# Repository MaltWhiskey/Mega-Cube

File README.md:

# Mega-Cube
16x16x16 PL9823 Cube with Teensy 4.0 and FlexIO driver
https://youtu.be/ciaFar8nfHc

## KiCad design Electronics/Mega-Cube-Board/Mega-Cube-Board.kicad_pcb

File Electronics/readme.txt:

Disclamer:
    These are my own electronic designs. You can use them however you like, but i take no
    responsibilty for them. It's up to you to use them well. 

Versions:
    32Bit shift register - This is my first iterration, i had some problems with them due to
    high frequency signals and using wires instead of pcb traces resulting in reflections.
    I have changed the software/hardware interface, so these may work, but i haven't tested this.

    32Bit shift register - This is the 2nd iterration. Fixed the reflexions and works flaweless
    for me. I recommond using JXT XH connectors and not dupont, since the touch screen can't handle
    iffy wiring. Just put a big cap i use 470uF near the power input. Other components are smd and
    you can have them assembled.
    Upload the Gerbers "32bit sr v2.0.zip" from the "32Bit SR Gerbers" folder to jlcpcb.com
    Turn on pcb assembly
    Upload the BOM-file "32Bit shift register.xlsx" from the "32Bit SR Assembly" folder
    Upload the CPL-file "32Bit shift register-all-pos.xlsx" from the "32Bit SR Assembly" folder
    Verify the components are in stock and place correctly.
    Order pcb

    Mega-Cube-Board - I wanted more functionality so i developed this board. The LCD can be soldered
    directly on this board without wires, so has more stability. It also has a buck converter and
    esp32's on it for gaming. A microphone and can drive speakers. The price to order this board
    was over $100 so i stopped working on it.

WARNING:
    The teensy 4.0 has no protection on the USB power. So powering through USB and a power supply
    may blow things up (I don't know because i'm carefull). You can use a usb cable and cut the 5V
    line. Or solder in a diode somewhere (look on pjrc site how to do that). Also never connect the
    5V power from the supplies together (I don't know what will happen, but probably real fireworks)
    All grounds from all power supplies must be tied together (NOT to the earth protective ground)
    If things are flickering you most likely have a disconnected wire or a grounding issue somewhere.

    Hope this clears thing up. Happy soldering.
    Malt Whiskey

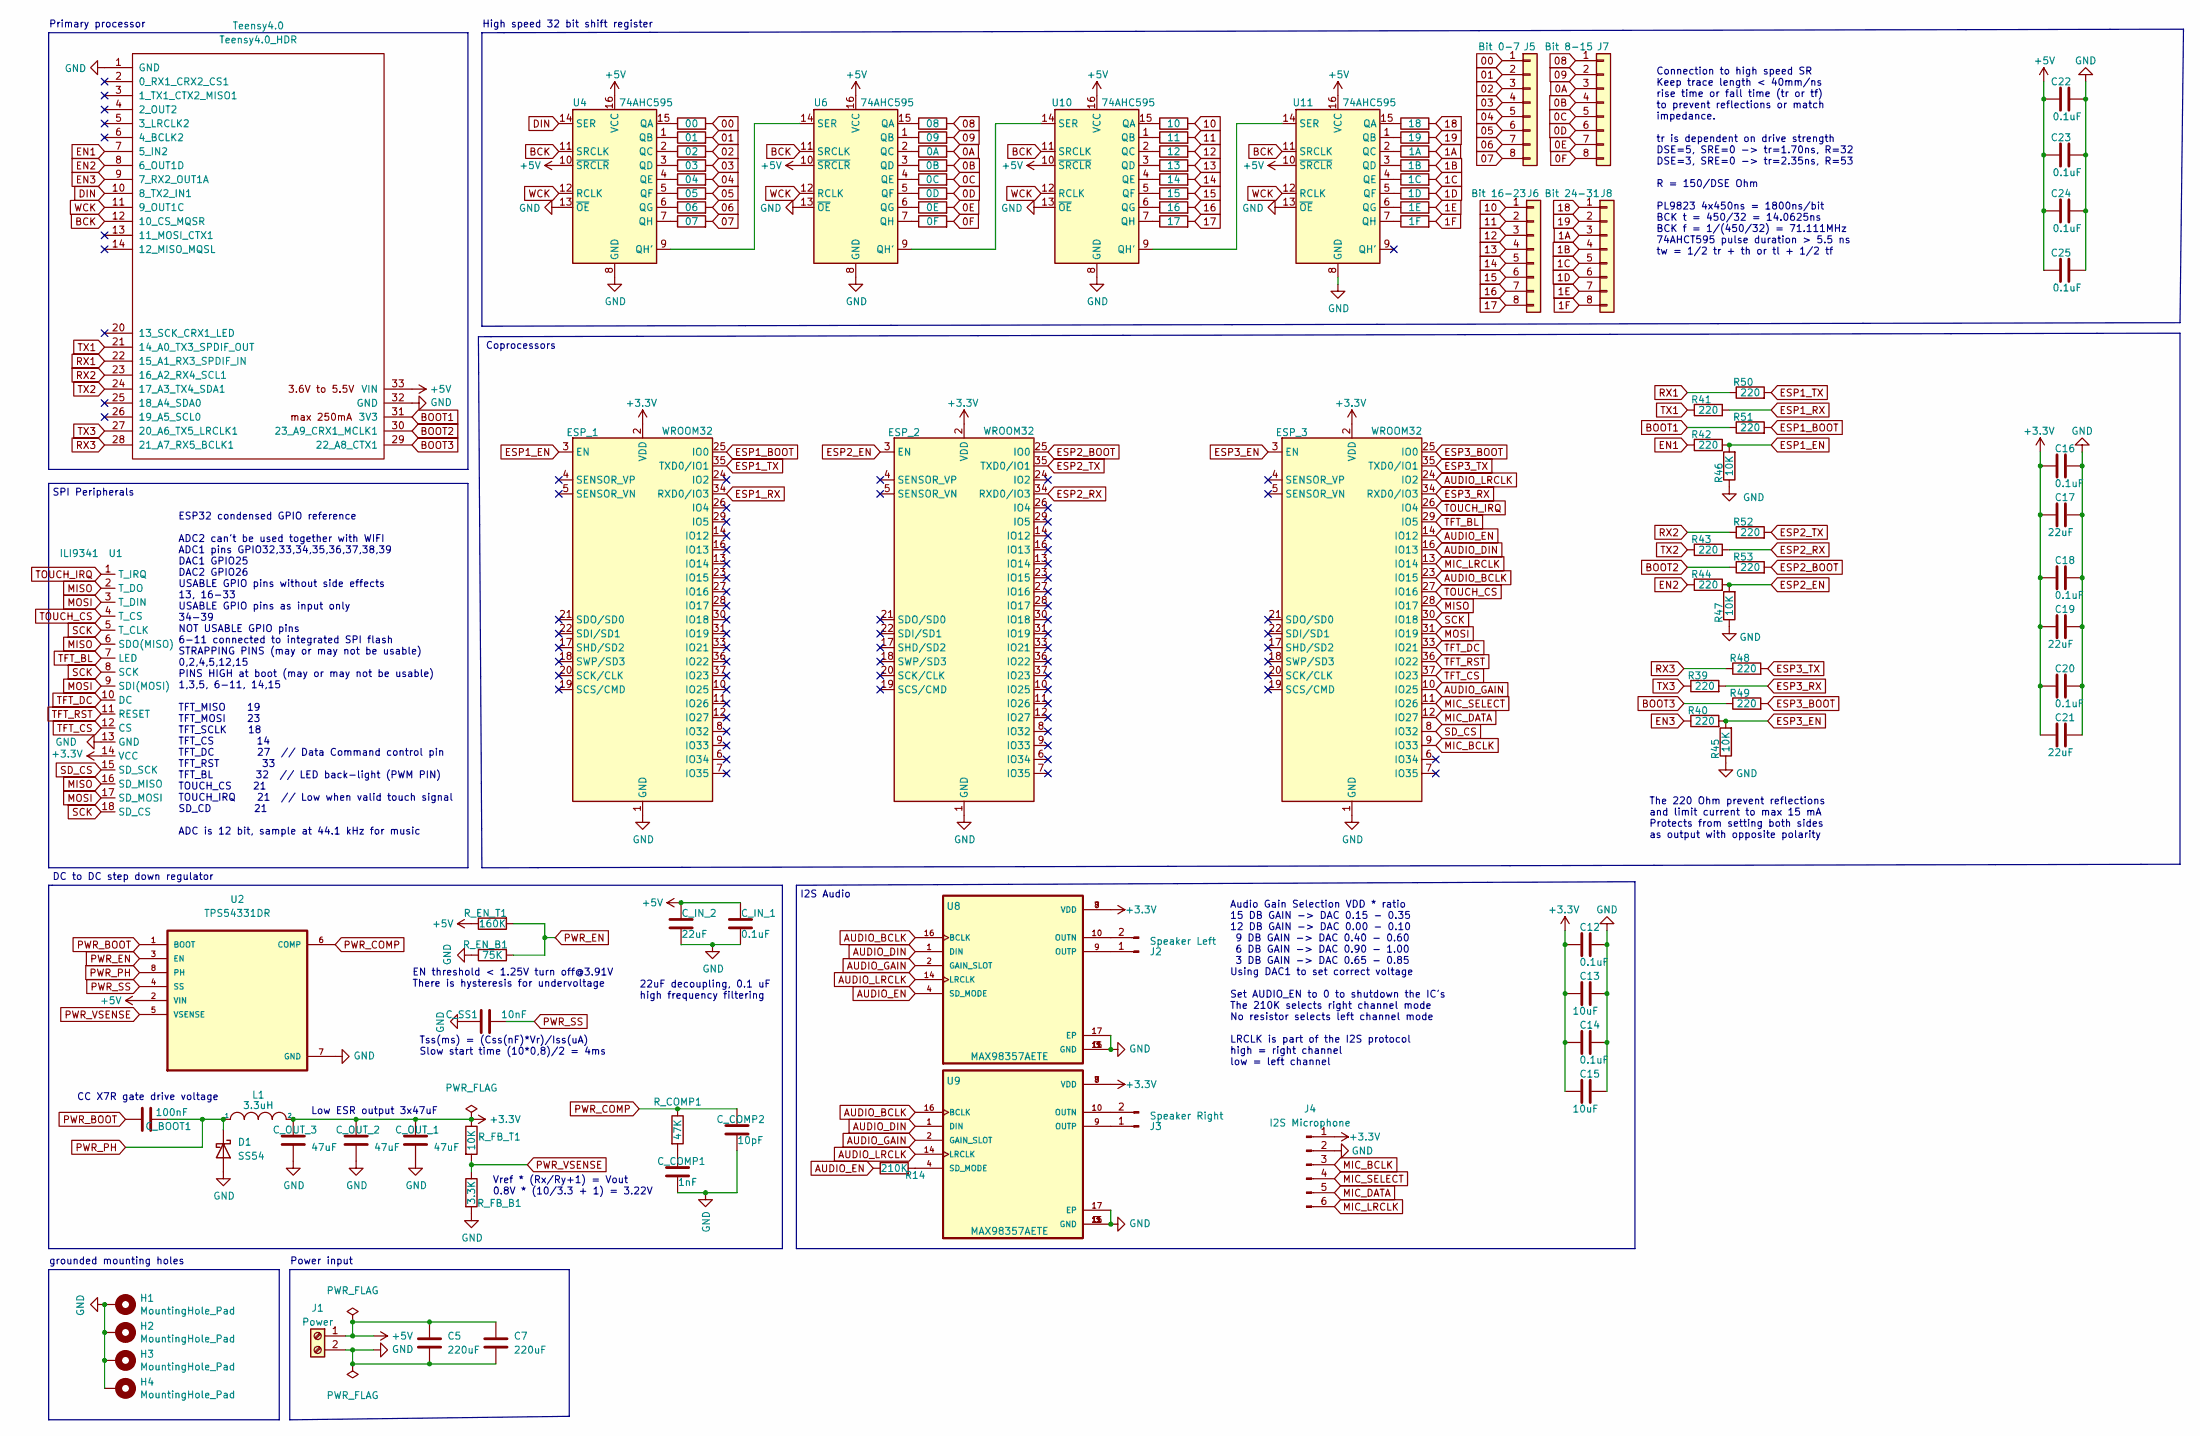
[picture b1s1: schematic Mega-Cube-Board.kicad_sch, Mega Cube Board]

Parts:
C5, C7: 220uF; CP_Radial_D8.0mm_P2.50mm
C12, C14: 0.1uF; C_0402_1005Metric; LCSC Part C307331
C13, C15: 10uF; C_0402_1005Metric; LCSC Part C15525
C16, C18, C20, C22, C23, C24, C25: 0.1uF; C_0603_1608Metric; LCSC Part C14663
C17, C19, C21: 22uF; C_0603_1608Metric; LCSC Part C59461
C_BOOT1: 100nF; C_0603_1608Metric; LCSC Part C14663
C_COMP1: 1nF; C_0603_1608Metric; LCSC Part C1588
C_COMP2: 10pF; C_0603_1608Metric; LCSC Part C1634
C_IN_1: 0.1uF; C_1206_3216Metric; LCSC Part C24497
C_IN_2: 22uF; C_1206_3216Metric; LCSC Part C12891
C_OUT_1, C_OUT_2, C_OUT_3: 47uF; C_1206_3216Metric; LCSC Part C96123
C_SS1: 10nF; C_0603_1608Metric; LCSC Part C57112
D1: SS54; D_SMA; LCSC Part C22452
ESP_1, ESP_2, ESP_3: WROOM32; ESP32-WROOM-32; LCSC Part C82899
H1, H2, H3, H4: MountingHole_Pad; MountingHole_3.2mm_M3_Pad_Via
J1: Power; TerminalBlock_bornier-2_P5.08mm
J2: Speaker Left; JST_XH_B2B-XH-A_1x02_P2.50mm_Vertical
J3: Speaker Right; JST_XH_B2B-XH-A_1x02_P2.50mm_Vertical
J4: I2S Microphone; JST_XH_B6B-XH-A_1x06_P2.50mm_Vertical
J5: Bit 0-7; JST_XH_B8B-XH-A_1x08_P2.50mm_Vertical
J6: Bit 16-23; JST_XH_B8B-XH-A_1x08_P2.50mm_Vertical
J7: Bit 8-15; JST_XH_B8B-XH-A_1x08_P2.50mm_Vertical
J8: Bit 24-31; JST_XH_B8B-XH-A_1x08_P2.50mm_Vertical
L1: 3.3uH; L_Sunltech_SLO0630H_7.1x6.6mm; LCSC Part C207839
R6, R7, R8, R9, R10, R11, R12, R13, R15, R16, R17, R18, R19, R20, R21, R22, R23, R24, R25, R26, R27, R28, R29, R30, R31, R32, R33, R34, R35, R36, R37, R38, R39, R40, R41, R42, R43, R44, R48, R49, R50, R51, R52, R53: 220; R_0402_1005Metric; LCSC Part C25091
R14: 210K; R_0402_1005Metric; LCSC Part C25767
R45, R46, R47: 10K; R_0402_1005Metric; LCSC Part C25744
R_COMP1: 47K; R_0603_1608Metric; LCSC Part C25819
R_EN_B1: 75K; R_0603_1608Metric; LCSC Part C23242
R_EN_T1: 160K; R_0603_1608Metric; LCSC Part C22813
R_FB_B1: 3.3K; R_0603_1608Metric; LCSC Part C22978
R_FB_T1: 10K; R_0603_1608Metric; LCSC Part C25804
Teensy4.0: Teensy4.0_HDR; Teensy40hdr
U1: ILI9341; ILI9341 2.4 TFT
U2: TPS54331DR; SOIC127P599X175-8N; LCSC Part C9865
U4, U6, U10, U11: 74AHC595; SOIC-16_3.9x9.9mm_P1.27mm; LCSC Part C133793
U8, U9: MAX98357AETE; QFN50P300X300X80-17N; LCSC Part C910544

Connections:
00: J5.1, R6.2
0A: J7.3, R17.2
0B: J7.4, R18.2
0C: J7.5, R19.2
0D: J7.6, R20.2
0E: J7.7, R21.2
0F: J7.8, R22.2
01: J5.2, R7.2
1A: J8.3, R33.2
1B: J8.4, R34.2
1C: J8.5, R35.2
1D: J8.6, R36.2
1E: J8.7, R37.2
1F: J8.8, R38.2
02: J5.3, R8.2
03: J5.4, R9.2
04: J5.5, R10.2
05: J5.6, R11.2
06: J5.7, R12.2
07: J5.8, R13.2
08: J7.1, R15.2
09: J7.2, R16.2
10: J6.1, R23.2
11: J6.2, R24.2
12: J6.3, R25.2
13: J6.4, R26.2
14: J6.5, R27.2
15: J6.6, R28.2
16: J6.7, R29.2
17: J6.8, R30.2
18: J8.1, R31.2
19: J8.2, R32.2
+3V3: C12.2, C13.2, C14.2, C15.2, C16.2, C17.2, C18.2, C19.2, C20.2, C21.2, C_OUT_1.1, C_OUT_2.1, C_OUT_3.1, ESP_1.2 (VDD), ESP_2.2 (VDD), ESP_3.2 (VDD), J4.1, L1.2, R_FB_T1.1, U1.14 (VCC), U8.7 (VDD), U8.8 (VDD), U9.7 (VDD), U9.8 (VDD)
+5V: C5.1, C7.1, C22.1, C23.1, C24.1, C25.1, C_IN_1.1, C_IN_2.1, J1.1, R_EN_T1.1, Teensy4.0.33 (VIN), U2.2 (VIN), U4.10 (~SRCLR), U4.16 (VCC), U6.10 (~SRCLR), U6.16 (VCC), U10.10 (~SRCLR), U10.16 (VCC), U11.10 (~SRCLR), U11.16 (VCC)
AUDIO_BCLK: ESP_3.23 (IO15), U8.16 (BCLK), U9.16 (BCLK)
AUDIO_DIN: ESP_3.16 (IO13), U8.1 (DIN), U9.1 (DIN)
AUDIO_EN: ESP_3.14 (IO12), R14.1, U8.4 (SD_MODE)
AUDIO_GAIN: ESP_3.10 (IO25), U8.2 (GAIN_SLOT), U9.2 (GAIN_SLOT)
AUDIO_LRCLK: ESP_3.24 (IO2), U8.14 (LRCLK), U9.14 (LRCLK)
BCK: Teensy4.0.12 (10_CS_MQSR), U4.11 (SRCLK), U6.11 (SRCLK), U10.11 (SRCLK), U11.11 (SRCLK)
BOOT1: R51.1, Teensy4.0.31 (3V3)
BOOT2: R53.1, Teensy4.0.30 (23_A9_CRX1_MCLK1)
BOOT3: R49.1, Teensy4.0.29 (22_A8_CTX1)
DIN: Teensy4.0.10 (8_TX2_IN1), U4.14 (SER)
EN1: R42.1, Teensy4.0.7 (5_IN2)
EN2: R44.1, Teensy4.0.8 (6_OUT1D)
EN3: R40.1, Teensy4.0.9 (7_RX2_OUT1A)
ESP1_BOOT: ESP_1.25 (IO0), R51.2
ESP1_EN: ESP_1.3 (EN), R42.2, R46.2
ESP1_RX: ESP_1.34 (RXD0/IO3), R41.2
ESP1_TX: ESP_1.35 (TXD0/IO1), R50.2
ESP2_BOOT: ESP_2.25 (IO0), R53.2
ESP2_EN: ESP_2.3 (EN), R44.2, R47.2
ESP2_RX: ESP_2.34 (RXD0/IO3), R43.2
ESP2_TX: ESP_2.35 (TXD0/IO1), R52.2
ESP3_BOOT: ESP_3.25 (IO0), R49.2
ESP3_EN: ESP_3.3 (EN), R40.2, R45.2
ESP3_RX: ESP_3.34 (RXD0/IO3), R39.2
ESP3_TX: ESP_3.35 (TXD0/IO1), R48.2
GND: C5.2, C7.2, C12.1, C13.1, C14.1, C15.1, C16.1, C17.1, C18.1, C19.1, C20.1, C21.1, C22.2, C23.2, C24.2, C25.2, C_COMP1.2, C_COMP2.2, C_IN_1.2, C_IN_2.2, C_OUT_1.2, C_OUT_2.2, C_OUT_3.2, C_SS1.1, D1.2 (A), ESP_1.1 (GND), ESP_1.15 (GND), ESP_1.38 (GND), ESP_1.39 (GND), ESP_2.1 (GND), ESP_2.15 (GND), ESP_2.38 (GND), ESP_2.39 (GND), ESP_3.1 (GND), ESP_3.15 (GND), ESP_3.38 (GND), ESP_3.39 (GND), H1.1, H2.1, H3.1, H4.1, J1.2, J4.2, R45.1, R46.1, R47.1, R_EN_B1.1, R_FB_B1.2, Teensy4.0.1 (GND), Teensy4.0.32 (GND), U1.13 (GND), U2.7 (GND), U4.8 (GND), U4.13 (~OE), U6.8 (GND), U6.13 (~OE), U8.3 (GND), U8.11 (GND), U8.15 (GND), U8.17 (EP), U9.3 (GND), U9.11 (GND), U9.15 (GND), U9.17 (EP), U10.8 (GND), U10.13 (~OE), U11.8 (GND), U11.13 (~OE)
MIC_BCLK: ESP_3.9 (IO33), J4.3
MIC_DATA: ESP_3.12 (IO27), J4.5
MIC_LRCLK: ESP_3.13 (IO14), J4.6
MIC_SELECT: ESP_3.11 (IO26), J4.4
MISO: ESP_3.28 (IO17), U1.2 (T_DO), U1.6 (SDO(MISO)), U1.16 (SD_MISO)
MOSI: ESP_3.31 (IO19), U1.3 (T_DIN), U1.9 (SDI(MOSI)), U1.17 (SD_MOSI)
unnamed: C_COMP1.1, R_COMP1.2
unnamed: J2.1, U8.9 (OUTP)
unnamed: J2.2, U8.10 (OUTN)
unnamed: J3.1, U9.9 (OUTP)
unnamed: J3.2, U9.10 (OUTN)
unnamed: R6.1, U4.15 (QA)
unnamed: R7.1, U4.1 (QB)
unnamed: R8.1, U4.2 (QC)
unnamed: R9.1, U4.3 (QD)
unnamed: R10.1, U4.4 (QE)
unnamed: R11.1, U4.5 (QF)
unnamed: R12.1, U4.6 (QG)
unnamed: R13.1, U4.7 (QH)
unnamed: R14.2, U9.4 (SD_MODE)
unnamed: R15.1, U6.15 (QA)
unnamed: R16.1, U6.1 (QB)
unnamed: R17.1, U6.2 (QC)
unnamed: R18.1, U6.3 (QD)
unnamed: R19.1, U6.4 (QE)
unnamed: R20.1, U6.5 (QF)
unnamed: R21.1, U6.6 (QG)
unnamed: R22.1, U6.7 (QH)
unnamed: R23.1, U10.15 (QA)
unnamed: R24.1, U10.1 (QB)
unnamed: R25.1, U10.2 (QC)
unnamed: R26.1, U10.3 (QD)
unnamed: R27.1, U10.4 (QE)
unnamed: R28.1, U10.5 (QF)
unnamed: R29.1, U10.6 (QG)
unnamed: R30.1, U10.7 (QH)
unnamed: R31.1, U11.15 (QA)
unnamed: R32.1, U11.1 (QB)
unnamed: R33.1, U11.2 (QC)
unnamed: R34.1, U11.3 (QD)
unnamed: R35.1, U11.4 (QE)
unnamed: R36.1, U11.5 (QF)
unnamed: R37.1, U11.6 (QG)
unnamed: R38.1, U11.7 (QH)
unnamed: U4.9 (QH'), U6.14 (SER)
unnamed: U10.9 (QH'), U11.14 (SER)
unnamed: U6.9 (QH'), U10.14 (SER)
PWR_BOOT: C_BOOT1.1, U2.1 (BOOT)
PWR_COMP: C_COMP2.1, R_COMP1.1, U2.6 (COMP)
PWR_EN: R_EN_B1.2, R_EN_T1.2, U2.3 (EN)
PWR_PH: C_BOOT1.2, D1.1 (K), L1.1, U2.8 (PH)
PWR_SS: C_SS1.2, U2.4 (SS)
PWR_VSENSE: R_FB_B1.1, R_FB_T1.2, U2.5 (VSENSE)
RX1: R50.1, Teensy4.0.22 (15_A1_RX3_SPDIF_IN)
RX2: R52.1, Teensy4.0.23 (16_A2_RX4_SCL1)
RX3: R48.1, Teensy4.0.28 (21_A7_RX5_BCLK1)
SCK: ESP_3.30 (IO18), U1.5 (T_CLK), U1.8 (SCK), U1.18 (SD_CS)
SD_CS: ESP_3.8 (IO32), U1.15 (SD_SCK)
TFT_BL: ESP_3.29 (IO5), U1.7 (LED)
TFT_CS: ESP_3.37 (IO23), U1.12 (CS)
TFT_DC: ESP_3.33 (IO21), U1.10 (DC)
TFT_RST: ESP_3.36 (IO22), U1.11 (RESET)
TOUCH_CS: ESP_3.27 (IO16), U1.4 (T_CS)
TOUCH_IRQ: ESP_3.26 (IO4), U1.1 (T_IRQ)
TX1: R41.1, Teensy4.0.21 (14_A0_TX3_SPDIF_OUT)
TX2: R43.1, Teensy4.0.24 (17_A3_TX4_SDA1)
TX3: R39.1, Teensy4.0.27 (20_A6_TX5_LRCLK1)
WCK: Teensy4.0.11 (9_OUT1C), U4.12 (RCLK), U6.12 (RCLK), U10.12 (RCLK), U11.12 (RCLK)

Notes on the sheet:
CC X7R gate drive voltage
SPI Peripherals
22uF decoupling, 0.1 uF high frequency filtering
ESP32 condensed GPIO reference ADC2 can't be used together with WIFI ADC1 pins GPIO32,33,34,35,36,37,38,39 DAC1 GPIO25 DAC2 GPIO26 USABLE GPIO pins without side effects 13, 16-33 USABLE GPIO pins as input only 34-39 NOT USABLE GPIO pins 6-11 connected to integrated SPI flash STRAPPING PINS (may or 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
Vref * (Rx/Ry+1) = Vout 0.8V * (10/3.3 + 1) = 3.22V
High speed 32 bit shift register
Power input
DC to DC step down regulator
Connection to high speed SR Keep trace length < 40mm/ns rise time or fall time (tr or tf) to prevent reflections or match impedance. tr is dependent on drive strength DSE=5, SRE=0 -> tr=1.70ns, R=32 DSE=3, SRE=0 -> tr=2.35ns, R=53 R = 150/DSE Ohm PL9823 4x450ns = 1800ns/bit BCK t = 450/32 = 14.0625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
The 220 Ohm prevent reflections and limit current to max 15 mA Protects from setting both sides as output with opposite polarity
grounded mounting holes
Tss(ms) = (Css(nF)*Vr)/Iss(uA) Slow start time (10*0,8)/2 = 4ms
EN threshold < 1.25V turn off@3.91V There is hysteresis for undervoltage
Audio Gain Selection VDD * ratio 15 DB GAIN -> DAC 0.15 - 0.35 12 DB GAIN -> DAC 0.00 - 0.10 9 DB GAIN -> DAC 0.40 - 0.60 6 DB GAIN -> DAC 0.90 - 1.00 3 DB GAIN -> DAC 0.65 - 0.85 Using DAC1 to set correct voltage Set AUDIO_EN to 0 to shutdown the IC's The 210K selects right channel mode No resisto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
Primary processor
Low ESR output 3x47uF
Coprocessors
I2S Audio

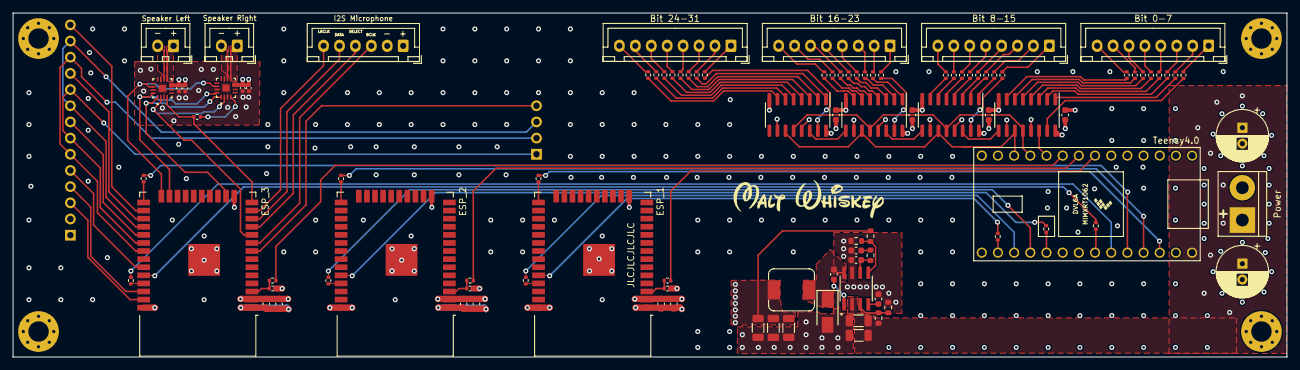
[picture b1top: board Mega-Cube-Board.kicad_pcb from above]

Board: 4 copper layers, 200.0 x 54.0 mm, 104 parts (0 on the bottom side), 128 nets.

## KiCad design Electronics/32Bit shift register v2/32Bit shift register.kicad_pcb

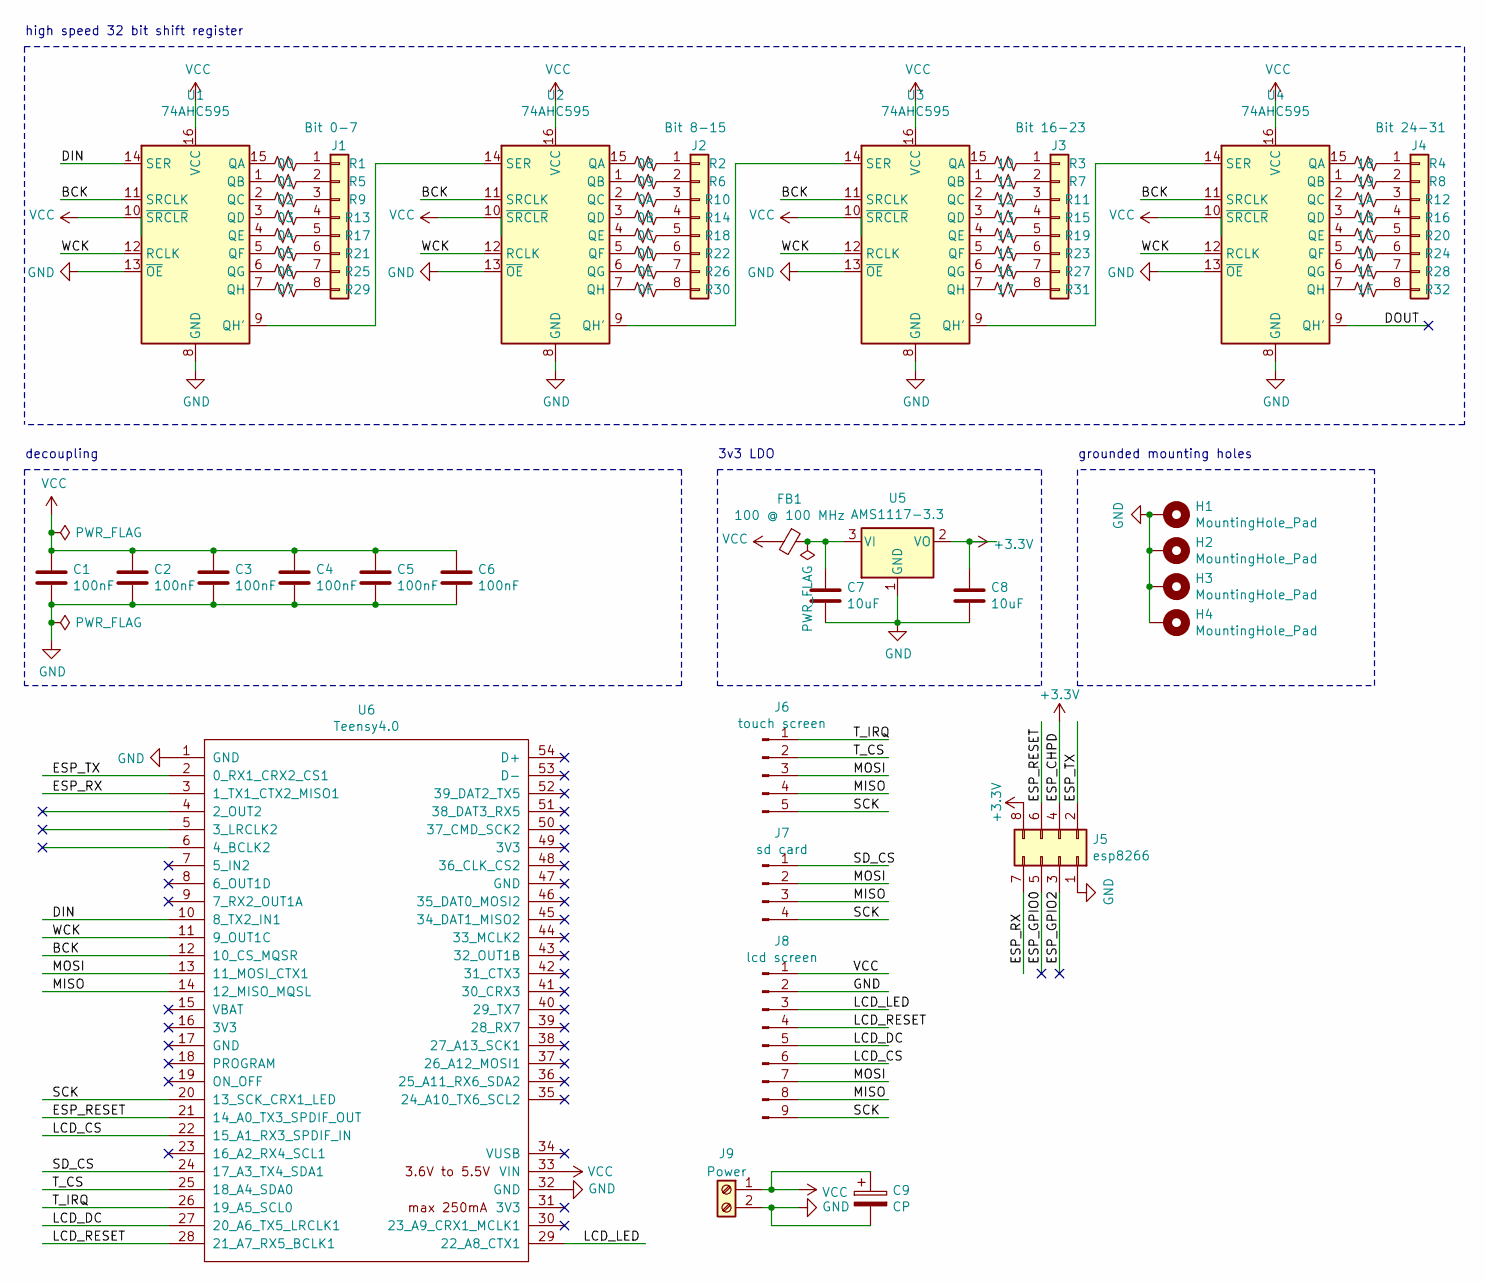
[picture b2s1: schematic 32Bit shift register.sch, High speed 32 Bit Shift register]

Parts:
C1, C2, C3, C4, C5, C6: 100nF; C_0603_1608Metric
C7, C8: 10uF; C_0603_1608Metric
C9: CP; CP_Radial_D8.0mm_P2.50mm
FB1: 100 @ 100 MHz; L_0805_2012Metric
H1, H2, H3, H4: MountingHole_Pad; MountingHole_3.2mm_M3_Pad_Via
J1: Bit 0-7; JST_XH_B8B-XH-A_1x08_P2.50mm_Vertical
J2: Bit 8-15; JST_XH_B8B-XH-A_1x08_P2.50mm_Vertical
J3: Bit 16-23; JST_XH_B8B-XH-A_1x08_P2.50mm_Vertical
J4: Bit 24-31; JST_XH_B8B-XH-A_1x08_P2.50mm_Vertical
J5: esp8266; PinSocket_2x04_P2.54mm_Vertical
J6: touch screen; JST_XH_B5B-XH-A_1x05_P2.50mm_Vertical
J7: sd card; JST_XH_B4B-XH-A_1x04_P2.50mm_Vertical
J8: lcd screen; JST_XH_B9B-XH-A_1x09_P2.50mm_Vertical
J9: Power; TerminalBlock_bornier-2_P5.08mm
R1: 00; R_0402_1005Metric
R2: 08; R_0402_1005Metric
R3: 10; R_0402_1005Metric
R4: 18; R_0402_1005Metric
R5: 01; R_0402_1005Metric
R6: 09; R_0402_1005Metric
R7: 11; R_0402_1005Metric
R8: 19; R_0402_1005Metric
R9: 02; R_0402_1005Metric
R10: 0A; R_0402_1005Metric
R11: 12; R_0402_1005Metric
R12: 1A; R_0402_1005Metric
R13: 03; R_0402_1005Metric
R14: 0B; R_0402_1005Metric
R15: 13; R_0402_1005Metric
R16: 1B; R_0402_1005Metric
R17: 04; R_0402_1005Metric
R18: 0C; R_0402_1005Metric
R19: 14; R_0402_1005Metric
R20: 1C; R_0402_1005Metric
R21: 05; R_0402_1005Metric
R22: 0D; R_0402_1005Metric
R23: 15; R_0402_1005Metric
R24: 1D; R_0402_1005Metric
R25: 06; R_0402_1005Metric
R26: 0E; R_0402_1005Metric
R27: 16; R_0402_1005Metric
R28: 1E; R_0402_1005Metric
R29: 07; R_0402_1005Metric
R30: 0F; R_0402_1005Metric
R31: 17; R_0402_1005Metric
R32: 1F; R_0402_1005Metric
U1, U2, U3, U4: 74AHC595; SOIC-16_3.9x9.9mm_P1.27mm
U5: AMS1117-3.3; SOT-223-3_TabPin2
U6: Teensy4.0; Teensy40hdr

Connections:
+3V3: C8.1, J5.4, J5.8, U5.2 (VO)
/BCK: U1.11 (SRCLK), U2.11 (SRCLK), U3.11 (SRCLK), U4.11 (SRCLK), U6.12 (10_CS_MQSR)
/DIN: U1.14 (SER), U6.10 (8_TX2_IN1)
/ESP_RESET: J5.6, U6.21 (14_A0_TX3_SPDIF_OUT)
/ESP_RX: J5.7, U6.3 (1_TX1_CTX2_MISO1)
/ESP_TX: J5.2, U6.2 (0_RX1_CRX2_CS1)
/LCD_CS: J8.6, U6.22 (15_A1_RX3_SPDIF_IN)
/LCD_DC: J8.5, U6.27 (20_A6_TX5_LRCLK1)
/LCD_LED: J8.3, U6.29 (22_A8_CTX1)
/LCD_RESET: J8.4, U6.28 (21_A7_RX5_BCLK1)
/MISO: J6.4, J7.3, J8.8, U6.14 (12_MISO_MQSL)
/MOSI: J6.3, J7.2, J8.7, U6.13 (11_MOSI_CTX1)
/SCK: J6.5, J7.4, J8.9, U6.20 (13_SCK_CRX1_LED)
/SD_CS: J7.1, U6.24 (17_A3_TX4_SDA1)
/T_CS: J6.2, U6.25 (18_A4_SDA0)
/T_IRQ: J6.1, U6.26 (19_A5_SCL0)
/WCK: U1.12 (RCLK), U2.12 (RCLK), U3.12 (RCLK), U4.12 (RCLK), U6.11 (9_OUT1C)
GND: C1.2, C2.2, C3.2, C4.2, C5.2, C6.2, C7.2, C8.2, C9.2, H1.1, H2.1, H3.1, H4.1, J5.1, J8.2, J9.2, U1.8 (GND), U1.13 (~OE), U2.8 (GND), U2.13 (~OE), U3.8 (GND), U3.13 (~OE), U4.8 (GND), U4.13 (~OE), U5.1 (GND), U6.1 (GND), U6.32 (GND)
unnamed 18: C7.1, FB1.1, U5.3 (VI); also elsewhere on the board
unnamed: J1.1, R1.1
unnamed: J1.2, R5.1
unnamed: J1.3, R9.1
unnamed: J1.4, R13.1
unnamed: J1.5, R17.1
unnamed: J1.6, R21.1
unnamed: J1.7, R25.1
unnamed: J1.8, R29.1
unnamed: J2.1, R2.1
unnamed: J2.2, R6.1
unnamed: J2.3, R10.1
unnamed: J2.4, R14.1
unnamed: J2.5, R18.1
unnamed: J2.6, R22.1
unnamed: J2.7, R26.1
unnamed: J2.8, R30.1
unnamed: J3.1, R3.1
unnamed: J3.2, R7.1
unnamed: J3.3, R11.1
unnamed: J3.4, R15.1
unnamed: J3.5, R19.1
unnamed: J3.6, R23.1
unnamed: J3.7, R27.1
unnamed: J3.8, R31.1
unnamed: J4.1, R4.1
unnamed: J4.2, R8.1
unnamed: J4.3, R12.1
unnamed: J4.4, R16.1
unnamed: J4.5, R20.1
unnamed: J4.6, R24.1
unnamed: J4.7, R28.1
unnamed: J4.8, R32.1
unnamed: R1.2, U1.15 (QA)
unnamed: R2.2, U2.15 (QA)
unnamed: R3.2, U3.15 (QA)
unnamed: R4.2, U4.15 (QA)
unnamed: R5.2, U1.1 (QB)
unnamed: R6.2, U2.1 (QB)
unnamed: R7.2, U3.1 (QB)
unnamed: R8.2, U4.1 (QB)
unnamed: R9.2, U1.2 (QC)
unnamed: R10.2, U2.2 (QC)
unnamed: R11.2, U3.2 (QC)
unnamed: R12.2, U4.2 (QC)
unnamed: R13.2, U1.3 (QD)
unnamed: R14.2, U2.3 (QD)
unnamed: R15.2, U3.3 (QD)
unnamed: R16.2, U4.3 (QD)
unnamed: R17.2, U1.4 (QE)
unnamed: R18.2, U2.4 (QE)
unnamed: R19.2, U3.4 (QE)
unnamed: R20.2, U4.4 (QE)
unnamed: R21.2, U1.5 (QF)
unnamed: R22.2, U2.5 (QF)
unnamed: R23.2, U3.5 (QF)
unnamed: R24.2, U4.5 (QF)
unnamed: R25.2, U1.6 (QG)
unnamed: R26.2, U2.6 (QG)
unnamed: R27.2, U3.6 (QG)
unnamed: R28.2, U4.6 (QG)
unnamed: R29.2, U1.7 (QH)
unnamed: R30.2, U2.7 (QH)
unnamed: R31.2, U3.7 (QH)
unnamed: R32.2, U4.7 (QH)
unnamed: U1.9 (QH'), U2.14 (SER)
unnamed: U2.9 (QH'), U3.14 (SER)
unnamed: U3.9 (QH'), U4.14 (SER)
VCC: C1.1, C2.1, C3.1, C4.1, C5.1, C6.1, C9.1, FB1.2, J8.1, J9.1, U1.10 (~SRCLR), U1.16 (VCC), U2.10 (~SRCLR), U2.16 (VCC), U3.10 (~SRCLR), U3.16 (VCC), U4.10 (~SRCLR), U4.16 (VCC), U6.33 (VIN); also elsewhere on the board

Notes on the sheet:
3v3 LDO
high speed 32 bit shift register
decoupling
grounded mounting holes

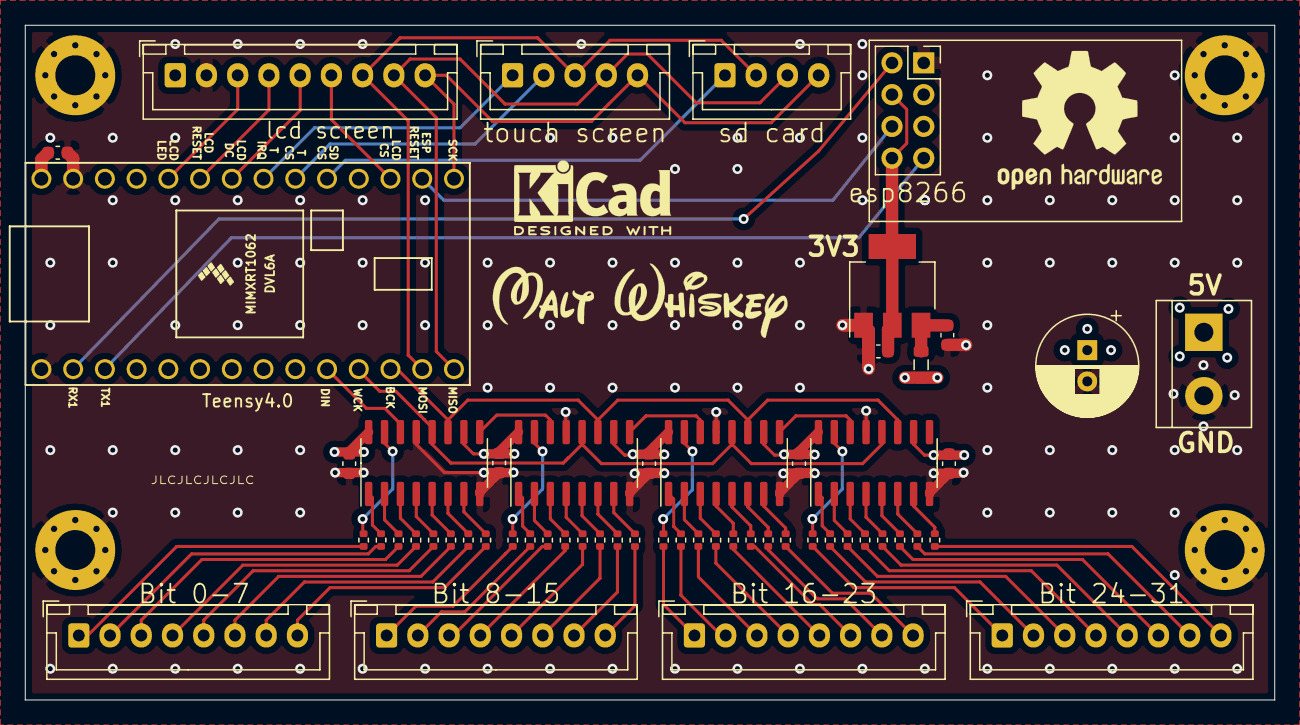
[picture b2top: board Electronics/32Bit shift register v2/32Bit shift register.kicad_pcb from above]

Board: 4 copper layers, 100.0 x 54.0 mm, 61 parts (0 on the bottom side), 87 nets.

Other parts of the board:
FB: 100 @ 100 MHz; L_0805_2012Metric

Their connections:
unnamed 18: FB.1; also elsewhere on the board
VCC: FB.2; also elsewhere on the board

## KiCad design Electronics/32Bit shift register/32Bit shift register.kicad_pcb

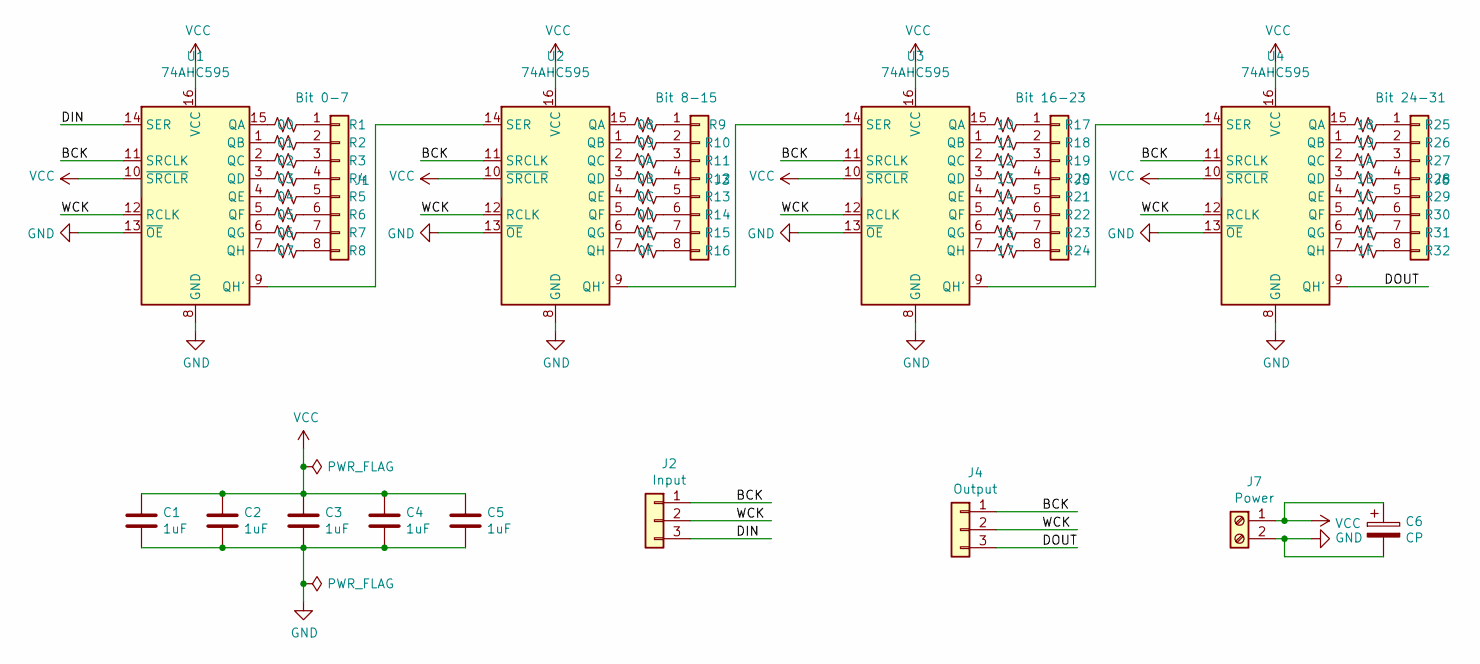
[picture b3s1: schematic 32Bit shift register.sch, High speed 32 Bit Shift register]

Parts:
C1, C2, C3, C4, C5: 1uF; C_Disc_D5.0mm_W2.5mm_P2.50mm
C6: CP; CP_Radial_D8.0mm_P2.50mm
J1: Bit 0-7; IDC-Header_2x04_P2.54mm_Vertical
J2: Input; PinHeader_1x03_P2.54mm_Vertical
J3: Bit 8-15; IDC-Header_2x04_P2.54mm_Vertical
J4: Output; PinHeader_1x03_P2.54mm_Vertical
J5: Bit 16-23; IDC-Header_2x04_P2.54mm_Vertical
J6: Bit 24-31; IDC-Header_2x04_P2.54mm_Vertical
J7: Power; TerminalBlock_bornier-2_P5.08mm
R1: 00; R_0805_2012Metric_Pad1.20x1.40mm_HandSolder
R2: 01; R_0805_2012Metric_Pad1.20x1.40mm_HandSolder
R3: 02; R_0805_2012Metric_Pad1.20x1.40mm_HandSolder
R4: 03; R_0805_2012Metric_Pad1.20x1.40mm_HandSolder
R5: 04; R_0805_2012Metric_Pad1.20x1.40mm_HandSolder
R6: 05; R_0805_2012Metric_Pad1.20x1.40mm_HandSolder
R7: 06; R_0805_2012Metric_Pad1.20x1.40mm_HandSolder
R8: 07; R_0805_2012Metric_Pad1.20x1.40mm_HandSolder
R9: 08; R_0805_2012Metric_Pad1.20x1.40mm_HandSolder
R10: 09; R_0805_2012Metric_Pad1.20x1.40mm_HandSolder
R11: 0A; R_0805_2012Metric_Pad1.20x1.40mm_HandSolder
R12: 0B; R_0805_2012Metric_Pad1.20x1.40mm_HandSolder
R13: 0C; R_0805_2012Metric_Pad1.20x1.40mm_HandSolder
R14: 0D; R_0805_2012Metric_Pad1.20x1.40mm_HandSolder
R15: 0E; R_0805_2012Metric_Pad1.20x1.40mm_HandSolder
R16: 0F; R_0805_2012Metric_Pad1.20x1.40mm_HandSolder
R17: 10; R_0805_2012Metric_Pad1.20x1.40mm_HandSolder
R18: 11; R_0805_2012Metric_Pad1.20x1.40mm_HandSolder
R19: 12; R_0805_2012Metric_Pad1.20x1.40mm_HandSolder
R20: 13; R_0805_2012Metric_Pad1.20x1.40mm_HandSolder
R21: 14; R_0805_2012Metric_Pad1.20x1.40mm_HandSolder
R22: 15; R_0805_2012Metric_Pad1.20x1.40mm_HandSolder
R23: 16; R_0805_2012Metric_Pad1.20x1.40mm_HandSolder
R24: 17; R_0805_2012Metric_Pad1.20x1.40mm_HandSolder
R25: 18; R_0805_2012Metric_Pad1.20x1.40mm_HandSolder
R26: 19; R_0805_2012Metric_Pad1.20x1.40mm_HandSolder
R27: 1A; R_0805_2012Metric_Pad1.20x1.40mm_HandSolder
R28: 1B; R_0805_2012Metric_Pad1.20x1.40mm_HandSolder
R29: 1C; R_0805_2012Metric_Pad1.20x1.40mm_HandSolder
R30: 1D; R_0805_2012Metric_Pad1.20x1.40mm_HandSolder
R31: 1E; R_0805_2012Metric_Pad1.20x1.40mm_HandSolder
R32: 1F; R_0805_2012Metric_Pad1.20x1.40mm_HandSolder
U1, U2, U3, U4: 74AHC595; DIP-16_W7.62mm_LongPads

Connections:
/BCK: J2.1, J4.1, U1.11 (SRCLK), U2.11 (SRCLK), U3.11 (SRCLK), U4.11 (SRCLK)
/DIN: J2.3, U1.14 (SER)
/DOUT: J4.3, U4.9 (QH')
/WCK: J2.2, J4.2, U1.12 (RCLK), U2.12 (RCLK), U3.12 (RCLK), U4.12 (RCLK)
GND: C1.2, C2.2, C3.2, C4.2, C5.2, C6.2, J7.2, U1.8 (GND), U1.13 (~OE), U2.8 (GND), U2.13 (~OE), U3.8 (GND), U3.13 (~OE), U4.8 (GND), U4.13 (~OE)
unnamed: J1.1, R1.1
unnamed: J1.2, R2.1
unnamed: J1.3, R3.1
unnamed: J1.4, R4.1
unnamed: J1.5, R5.1
unnamed: J1.6, R6.1
unnamed: J1.7, R7.1
unnamed: J1.8, R8.1
unnamed: J3.1, R9.1
unnamed: J3.2, R10.1
unnamed: J3.3, R11.1
unnamed: J3.4, R12.1
unnamed: J3.5, R13.1
unnamed: J3.6, R14.1
unnamed: J3.7, R15.1
unnamed: J3.8, R16.1
unnamed: J5.1, R17.1
unnamed: J5.2, R18.1
unnamed: J5.3, R19.1
unnamed: J5.4, R20.1
unnamed: J5.5, R21.1
unnamed: J5.6, R22.1
unnamed: J5.7, R23.1
unnamed: J5.8, R24.1
unnamed: J6.1, R25.1
unnamed: J6.2, R26.1
unnamed: J6.3, R27.1
unnamed: J6.4, R28.1
unnamed: J6.5, R29.1
unnamed: J6.6, R30.1
unnamed: J6.7, R31.1
unnamed: J6.8, R32.1
unnamed: R1.2, U1.15 (QA)
unnamed: R2.2, U1.1 (QB)
unnamed: R3.2, U1.2 (QC)
unnamed: R4.2, U1.3 (QD)
unnamed: R5.2, U1.4 (QE)
unnamed: R6.2, U1.5 (QF)
unnamed: R7.2, U1.6 (QG)
unnamed: R8.2, U1.7 (QH)
unnamed: R9.2, U2.15 (QA)
unnamed: R10.2, U2.1 (QB)
unnamed: R11.2, U2.2 (QC)
unnamed: R12.2, U2.3 (QD)
unnamed: R13.2, U2.4 (QE)
unnamed: R14.2, U2.5 (QF)
unnamed: R15.2, U2.6 (QG)
unnamed: R16.2, U2.7 (QH)
unnamed: R17.2, U3.15 (QA)
unnamed: R18.2, U3.1 (QB)
unnamed: R19.2, U3.2 (QC)
unnamed: R20.2, U3.3 (QD)
unnamed: R21.2, U3.4 (QE)
unnamed: R22.2, U3.5 (QF)
unnamed: R23.2, U3.6 (QG)
unnamed: R24.2, U3.7 (QH)
unnamed: R25.2, U4.15 (QA)
unnamed: R26.2, U4.1 (QB)
unnamed: R27.2, U4.2 (QC)
unnamed: R28.2, U4.3 (QD)
unnamed: R29.2, U4.4 (QE)
unnamed: R30.2, U4.5 (QF)
unnamed: R31.2, U4.6 (QG)
unnamed: R32.2, U4.7 (QH)
unnamed: U1.9 (QH'), U2.14 (SER)
unnamed: U2.9 (QH'), U3.14 (SER)
unnamed: U3.9 (QH'), U4.14 (SER)
VCC: C1.1, C2.1, C3.1, C4.1, C5.1, C6.1, J7.1, U1.10 (~SRCLR), U1.16 (VCC), U2.10 (~SRCLR), U2.16 (VCC), U3.10 (~SRCLR), U3.16 (VCC), U4.10 (~SRCLR), U4.16 (VCC)

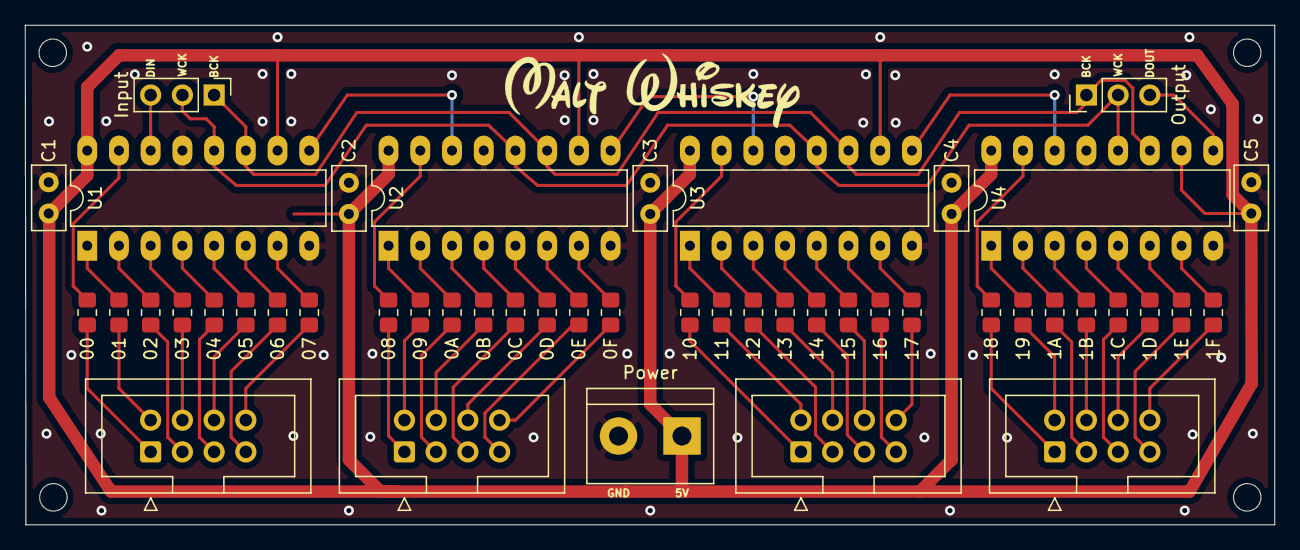
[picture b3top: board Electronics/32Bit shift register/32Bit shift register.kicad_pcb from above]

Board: 2 copper layers, 100.1 x 40.0 mm, 48 parts (0 on the bottom side), 73 nets.

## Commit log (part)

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2021-04-24 new test
2021-04-24 ignore
2021-04-24 .DS_Store banished!
2021-04-25 removed
2021-05-01 Before refactoring
2021-05-09 Revision
2021-05-12 Optimize display update
2021-05-16 Demien
2021-11-04 Added STL files
2021-11-05 Fixed overhang
2021-11-12 Removed singleton, added config
2021-11-12 added animations
2021-11-19 Quaternion and Perlin Noise
2021-11-29 Rotating mario example
2021-12-03 Game of Life
2021-12-08 Added Wifi and LCD (SPI and FLEXIO conflict?)
2022-07-15 Big Update
2022-07-15 removed folder
2022-07-15 Added Folder
2022-07-15 include
2022-07-15 Better font
2022-07-15 LCD TEST
2022-07-15 DMAMEM used
2022-07-28 GUI Update
2022-08-01 Settings and jump tabel improved
2022-08-01 clean up
2022-08-02 GUI editor files included
2022-08-02 Gui prepe
2022-08-03 Minimal GUI done
2022-08-03 Bug fix
2022-08-03 fixed timer
2022-08-04 button fix
2022-08-04 End animations improved
2022-08-04 dma fix
2022-08-04 Brightness Slider
2022-08-04 2nd slider
2022-08-05 Motion blur and labels update
2023-02-13 Added firmware binaries
2023-05-08 cosmetic
2023-08-31 Instructions for PCB added
2023-09-01 config change
2023-09-08 refactor for scaling
2023-12-27 better math
2024-07-10 Refactoring
2024-07-10 refactor
